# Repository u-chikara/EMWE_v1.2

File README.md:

# EMWE_v1.2

2024年度NHK高専ロボコンに出場したロボット「ひまり」と「ほしかご」に搭載していたメインマイコンボードの設計図です。

メインプロセッサ：ATSAME54N19A
統合開発環境：MPLAB

主な機能

CAN-FD 2チャンネル

SERCOM 5チャンネル（そのうち2チャンネルはコントローラと液晶用）

一応９軸IMUも付けられる

100M Ethernet

USB OTG （Type-CとTypeAをスイッチで切り替え）

SD/MMCカードスロット　マイコンに専用の回路があるのでそれで通信する

LEDとタクトスイッチをそれぞれ３つ搭載

今後のロボコンにお役立てください。

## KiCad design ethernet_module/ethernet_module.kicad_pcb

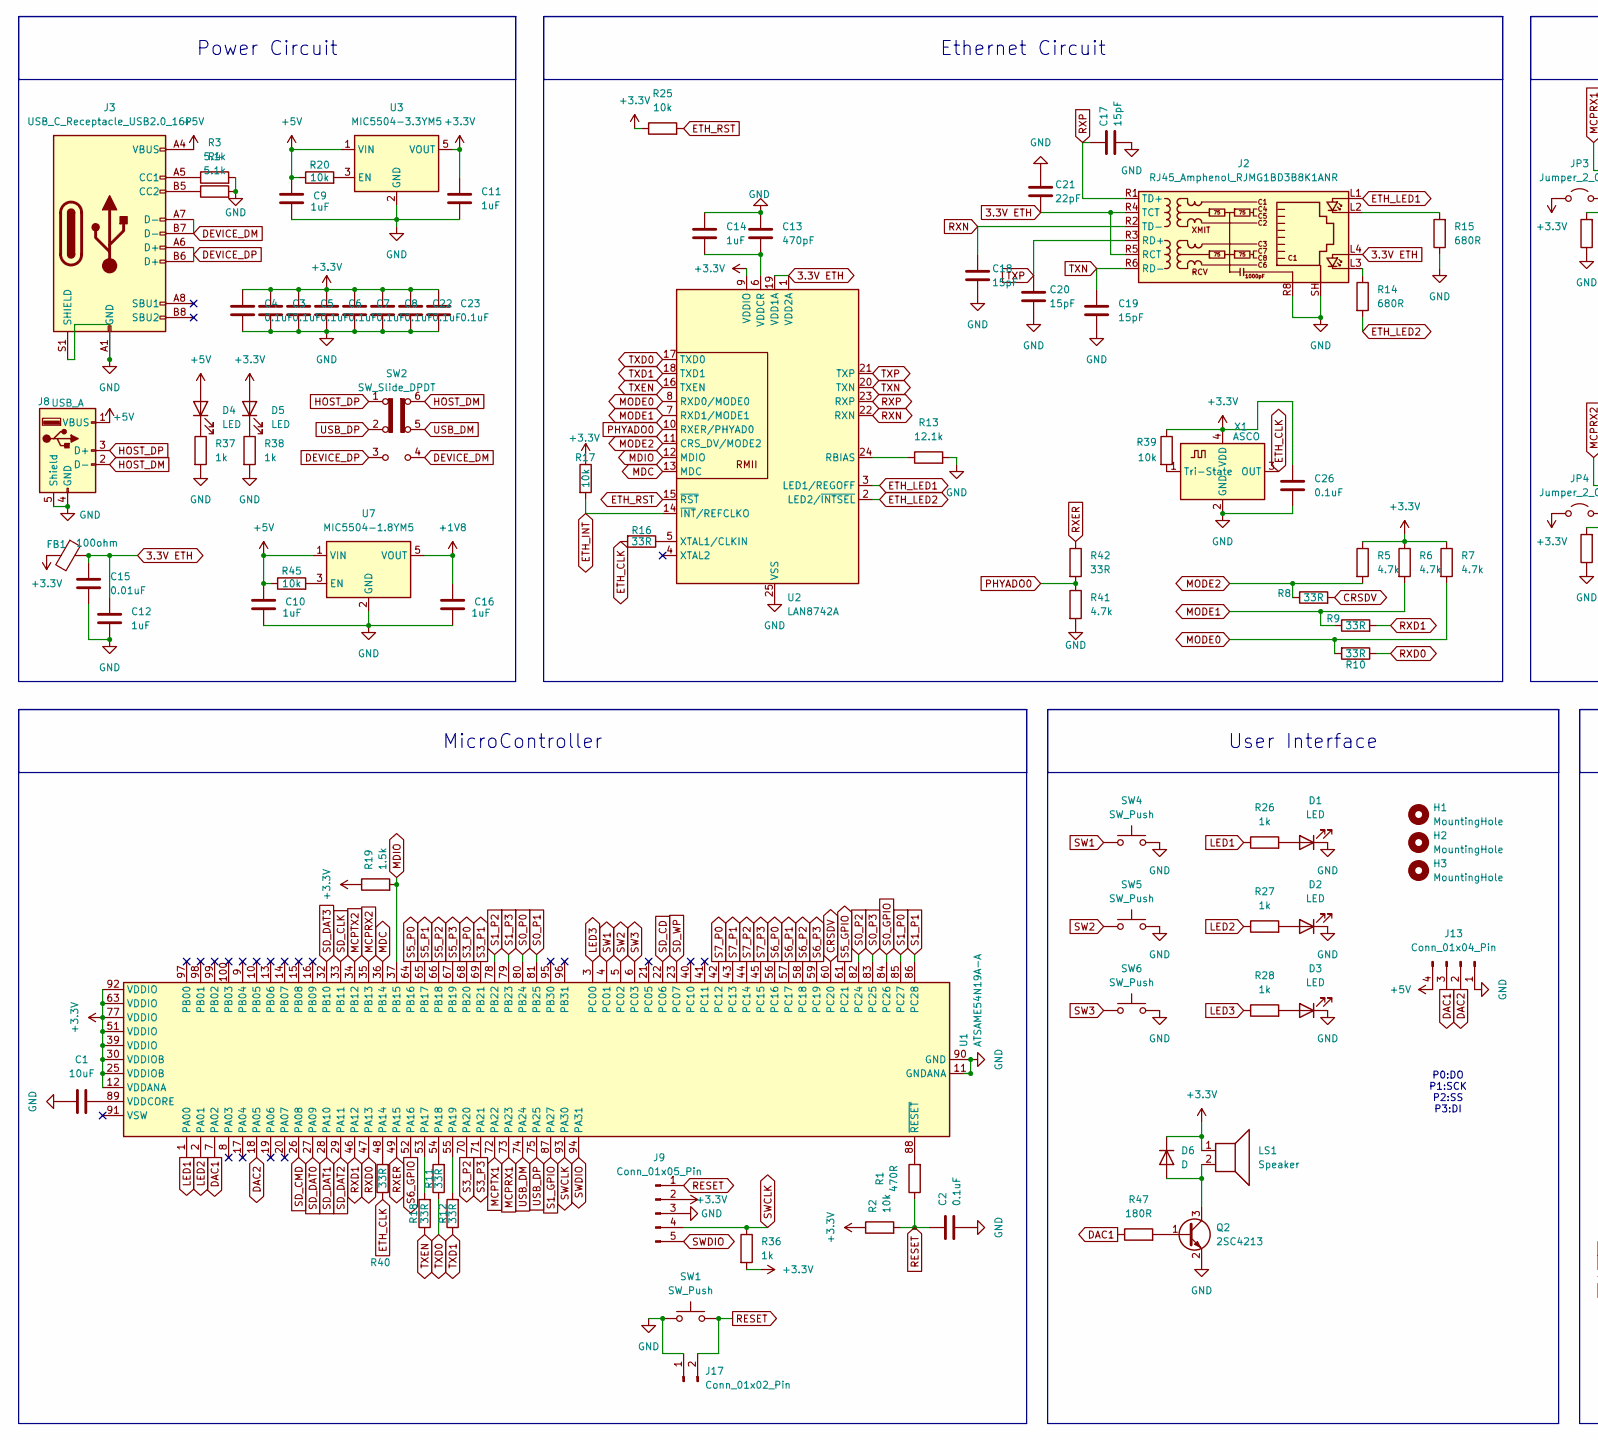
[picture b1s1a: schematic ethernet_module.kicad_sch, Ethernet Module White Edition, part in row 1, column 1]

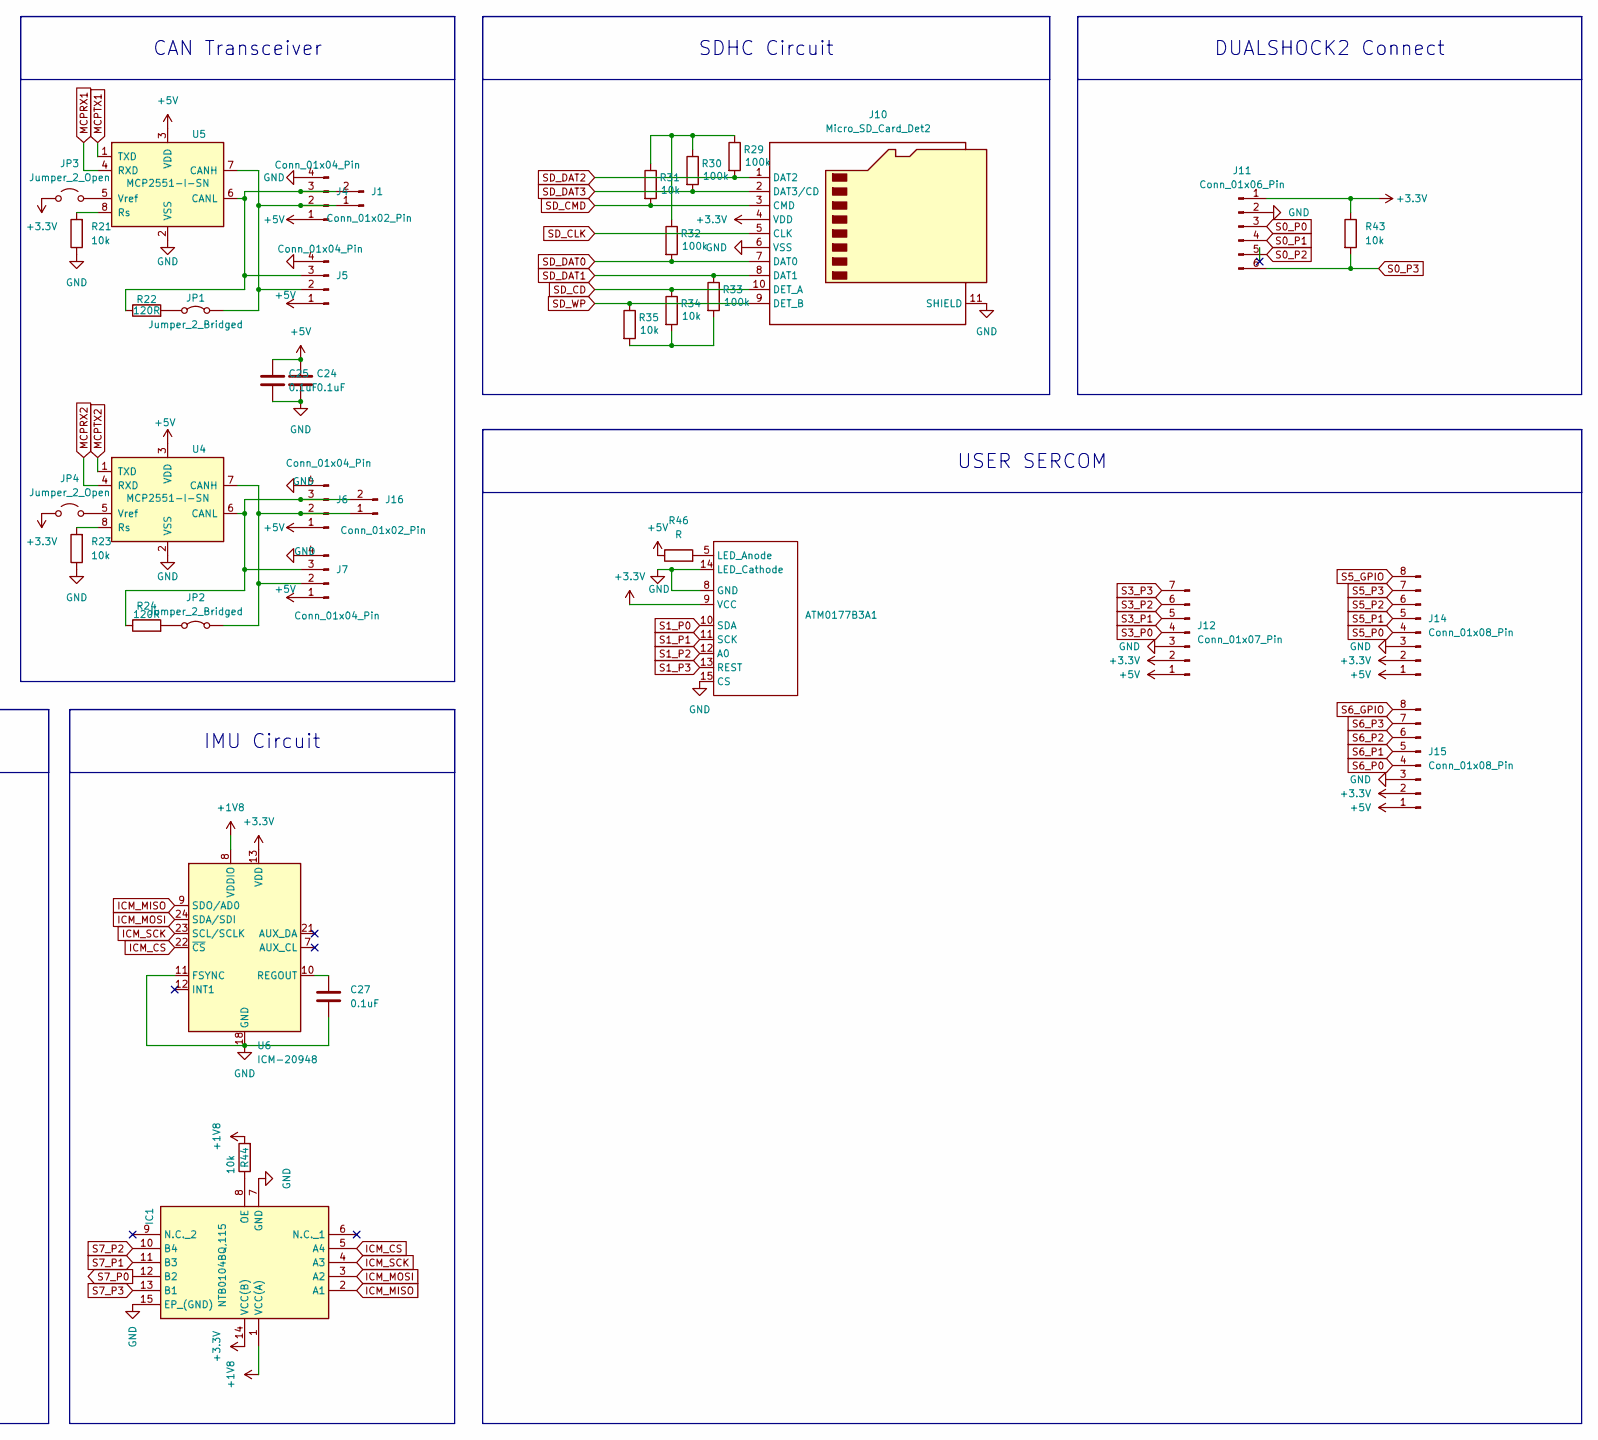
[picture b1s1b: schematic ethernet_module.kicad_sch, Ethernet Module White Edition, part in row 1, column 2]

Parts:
ATM0177B3A1: ATM0177B3A
C1: 10uF; R_0805_2012Metric
C2, C3, C4, C5, C6, C7, C8, C22, C23, C24, C25, C26, C27: 0.1uF; R_0603_1608Metric
C9, C10, C11, C12, C14, C16: 1uF; R_0603_1608Metric
C13: 470pF; R_0603_1608Metric
C15: 0.01uF; R_0603_1608Metric
C17, C18, C19, C20: 15pF; R_0603_1608Metric
C21: 22pF; R_0603_1608Metric
D1, D2, D3, D4, D5: LED; LED_0603_1608Metric
D6: D; D_0603_1608Metric
FB1: 100ohm; R_0603_1608Metric
H1, H2, H3: MountingHole; MountingHole_2.2mm_M2_Pad
IC1: NTB0104BQ,115; NTB0104BQ115; Manufacturer_Part_Number NTB0104BQ,115; Mouser Part Number 771-NTB0104BQ115
J1, J16, J17: Conn_01x02_Pin; PinHeader_1x02_P2.54mm_Vertical
J2: RJ45_Amphenol_RJMG1BD3B8K1ANR
J3: USB_C_Receptacle_USB2.0_16P; USB_C_Receptacle_GCT_USB4105-xx-A_16P_TopMnt_Horizontal
J4, J6: Conn_01x04_Pin; JST_XA_S04B-XASK-1_1x04_P2.50mm_Horizontal
J5, J7: Conn_01x04_Pin; JST_XA_B04B-XASK-1_1x04_P2.50mm_Vertical
J8: USB_A; USB_A_CONNFLY_DS1095-WNR0
J9: Conn_01x05_Pin; JST_PH_B5B-PH-K_1x05_P2.00mm_Vertical
J10: Micro_SD_Card_Det2; microSD_HC_Hirose_DM3AT-SF-PEJM5
J11: Conn_01x06_Pin; PinHeader_1x06_P1.27mm_Vertical
J12: Conn_01x07_Pin; PinHeader_1x07_P1.27mm_Vertical
J13: Conn_01x04_Pin; PinHeader_1x04_P1.27mm_Vertical
J14, J15: Conn_01x08_Pin; PinHeader_1x08_P1.27mm_Vertical
JP1, JP2: Jumper_2_Bridged; SolderJumper-2_P1.3mm_Open_RoundedPad1.0x1.5mm
JP3, JP4: Jumper_2_Open; SolderJumper-2_P1.3mm_Open_RoundedPad1.0x1.5mm
LS1: Speaker; PUIAudio_SMT_0825_S_4_R
Q2: 2SC4213; SOT-323_SC-70
R1: 470R; R_0603_1608Metric
R2, R17, R20, R21, R23, R25, R31, R34, R35, R39, R43, R44, R45: 10k; R_0603_1608Metric
R3, R4: 5.1k; R_0603_1608Metric
R5, R6, R7, R41: 4.7k; R_0603_1608Metric
R8, R9, R10, R11, R12, R16, R18, R40, R42: 33R; R_0603_1608Metric
R13: 12.1k; R_0603_1608Metric
R14, R15: 680R; R_0603_1608Metric
R19: 1.5k; R_0603_1608Metric
R22, R24: 120R; R_0603_1608Metric
R26, R27, R28, R36, R37, R38: 1k; R_0603_1608Metric
R29, R30, R32, R33: 100k; R_0603_1608Metric
R46: R; R_0603_1608Metric
R47: 180R; R_0603_1608Metric
SW1, SW4, SW5, SW6: SW_Push; SW_Push_1P1T_NO_CK_KMR2
SW2: SW_Slide_DPDT; SW_CK_JS202011CQN_DPDT_Straight
U1: ATSAME54N19A-A; TQFP-100_14x14mm_P0.5mm
U2: LAN8742A; VQFN-24-1EP_4x4mm_P0.5mm_EP2.5x2.5mm_ThermalVias
U3: MIC5504-3.3YM5; SOT-23-5
U4, U5: MCP2551-I-SN; SOIC-8_3.9x4.9mm_P1.27mm
U6: ICM-20948; InvenSense_QFN-24_3x3mm_P0.4mm
U7: MIC5504-1.8YM5; SOT-23-5
X1: ASCO; Oscillator_SMD_Abracon_ASE-4Pin_3.2x2.5mm

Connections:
3.3V ETH: C12.1, C15.1, C21.2, FB1.1, J2.L4, J2.R4 (TCT), J2.R5 (RCT), U2.1 (VDD2A), U2.19 (VDD1A)
+1V8: C16.1, IC1.1 (VCC(A)), R44.2, U6.8 (VDDIO), U7.5 (VOUT)
+3.3V: ATM0177B3A1.9 (VCC), C3.1, C4.1, C5.1, C6.1, C7.1, C8.1, C11.1, C22.1, C23.1, C26.1, D5.2 (A), D6.1 (K), FB1.2, IC1.14 (VCC(B)), J9.2, J10.4 (VDD), J11.1, J12.2, J14.2, J15.2, JP3.1 (A), JP4.1 (A), LS1.1, R2.1, R5.1, R6.1, R7.1, R17.1, R19.1, R25.1, R36.2, R39.1, R43.1, U1.12 (VDDANA), U1.25 (VDDIOB), U1.30 (VDDIOB), U1.39 (VDDIO), U1.51 (VDDIO), U1.63 (VDDIO), U1.77 (VDDIO), U1.92 (VDDIO), U2.9 (VDDIO), U3.5 (VOUT), U6.13 (VDD), X1.4 (VDD)
+5V: C9.1, C10.1, C24.1, C25.1, D4.2 (A), J3.A4 (VBUS), J3.A9 (VBUS), J3.B4 (VBUS), J3.B9 (VBUS), J4.1, J5.1, J6.1, J7.1, J8.1 (VBUS), J12.1, J13.4, J14.1, J15.1, R20.1, R45.1, R46.1, U3.1 (VIN), U4.3 (VDD), U5.3 (VDD), U7.1 (VIN)
CRSDV: R8.2, U1.60 (PC20)
DAC1: J13.3, R47.1, U1.7 (PA02)
DAC2: J13.2, U1.18 (PA05)
DEVICE_DM: J3.A7 (D-), J3.B7 (D-), SW2.4 (A)
DEVICE_DP: J3.A6 (D+), J3.B6 (D+), SW2.3 (C)
ETH_CLK: R16.2, R40.1, X1.3 (OUT)
ETH_INT: R17.2, U2.14 (~INT/REFCLKO)
ETH_LED1: J2.L1, U2.3 (LED1/REGOFF)
ETH_LED2: R14.2, U2.2 (LED2/~INTSEL)
ETH_RST: R25.2, U2.15 (~RST)
GND: ATM0177B3A1.8 (GND), ATM0177B3A1.14 (LED_Cathode), ATM0177B3A1.15 (CS), C1.1, C2.2, C3.2, C4.2, C5.2, C6.2, C7.2, C8.2, C9.2, C10.2, C11.2, C12.2, C13.1, C14.1, C15.2, C16.2, C17.2, C18.2, C19.2, C20.2, C21.1, C22.2, C23.2, C24.2, C25.2, C26.2, C27.2, D1.1 (K), D2.1 (K), D3.1 (K), IC1.7 (GND), IC1.15 (EP_(GND)), J2.R8, J2.SH, J3.A1 (GND), J3.A12 (GND), J3.B1 (GND), J3.B12 (GND), J3.S1 (SHIELD), J4.4, J5.4, J6.4, J7.4, J8.4 (GND), J8.5 (Shield), J9.3, J10.6 (VSS), J10.11 (SHIELD), J11.2, J12.3, J13.1, J14.3, J15.3, J17.1, Q2.2 (E), R3.2, R4.2, R13.2, R15.1, R21.1, R23.1, R37.2, R38.2, R41.2, SW1.1, SW4.2, SW5.2, SW6.2, U1.11 (GNDANA), U1.24 (GND), U1.31 (GND), U1.38 (GND), U1.50 (GND), U1.62 (GND), U1.76 (GND), U1.90 (GND), U2.25 (VSS), U3.2 (GND), U4.2 (VSS), U5.2 (VSS), U6.11 (FSYNC), U6.18 (GND), U6.20 (GND), U7.2 (GND), X1.2 (GND)
HOST_DM: J8.2 (D-), SW2.6 (C)
HOST_DP: J8.3 (D+), SW2.1 (A)
ICM_CS: IC1.5 (A4), U6.22 (~CS)
ICM_MISO: IC1.2 (A1), U6.9 (SDO/AD0)
ICM_MOSI: IC1.3 (A2), U6.24 (SDA/SDI)
ICM_SCK: IC1.4 (A3), U6.23 (SCL/SCLK)
LED1: R26.1, U1.1 (PA00)
LED2: R27.1, U1.2 (PA01)
LED3: R28.1, U1.3 (PC00)
MCPRX1: U1.73 (PA23), U5.4 (RXD)
MCPRX2: U1.35 (PB13), U4.4 (RXD)
MCPTX1: U1.72 (PA22), U5.1 (TXD)
MCPTX2: U1.34 (PB12), U4.1 (TXD)
MDC: U1.36 (PB14), U2.13 (MDC)
MDIO: R19.2, U1.37 (PB15), U2.12 (MDIO)
MODE0: R7.2, R10.2, U2.8 (RXD0/MODE0)
MODE1: R6.2, R9.1, U2.7 (RXD1/MODE1)
MODE2: R5.2, R8.1, U2.11 (CRS_DV/MODE2)
unnamed: ATM0177B3A1.5 (LED_Anode), R46.2
unnamed: D1.2 (A), R26.2
unnamed: D2.2 (A), R27.2
unnamed: D3.2 (A), R28.2
unnamed: D4.1 (K), R37.1
unnamed: D5.1 (K), R38.1
unnamed: D6.2 (A), LS1.2, Q2.3 (C)
unnamed: IC1.8 (OE), R44.1
unnamed: J1.1, J4.2, J5.2, JP1.2 (B), U5.7 (CANH)
unnamed: J1.2, J4.3, J5.3, R22.1, U5.6 (CANL)
unnamed: J2.L2, R15.2
unnamed: J2.L3, R14.1
unnamed: J3.A5 (CC1), R3.1
unnamed: J3.B5 (CC2), R4.1
unnamed: J6.2, J7.2, J16.1, JP2.2 (B), U4.7 (CANH)
unnamed: J6.3, J7.3, J16.2, R24.1, U4.6 (CANL)
unnamed: JP1.1 (A), R22.2
unnamed: JP2.1 (A), R24.2
unnamed: JP3.2 (B), U5.5 (Vref)
unnamed: JP4.2 (B), U4.5 (Vref)
unnamed: Q2.1 (B), R47.2
unnamed: R29.1, R30.1, R31.1, R32.1
unnamed: R33.2, R34.2, R35.2
unnamed: R40.2, U1.48 (PA14)
unnamed: R18.2, U1.53 (PA17)
unnamed: R11.2, U1.54 (PA18)
unnamed: R12.2, U1.55 (PA19)
unnamed: C1.2, U1.89 (VDDCORE)
unnamed: R1.2, U1.88 (~RESET)
unnamed: R13.1, U2.24 (RBIAS)
unnamed: C13.2, C14.2, U2.6 (VDDCR)
unnamed: R16.1, U2.5 (XTAL1/CLKIN)
unnamed: R20.2, U3.3 (EN)
unnamed: R23.2, U4.8 (Rs)
unnamed: R21.2, U5.8 (Rs)
unnamed: C27.1, U6.10 (REGOUT)
unnamed: R45.2, U7.3 (EN)
unnamed: R39.2, X1.1 (Tri-State)
PHYADO0: R41.1, R42.2, U2.10 (RXER/PHYAD0)
RESET: C2.1, J9.1, J17.2, R1.1, R2.2, SW1.2
RXD0: R10.1, U1.47 (PA13)
RXD1: R9.2, U1.46 (PA12)
RXER: R42.1, U1.49 (PA15)
RXN: C18.1, J2.R2 (TD-), U2.22 (RXN)
RXP: C17.1, J2.R1 (TD+), U2.23 (RXP)
S0_GPIO: U1.84 (PC26)
S0_P0: J11.3, U1.80 (PB24)
S0_P1: J11.4, U1.81 (PB25)
S0_P2: J11.5, U1.82 (PC24)
S0_P3: J11.6, R43.2, U1.83 (PC25)
S1_GPIO: U1.87 (PA27)
S1_P0: ATM0177B3A1.10 (SDA), U1.85 (PC27)
S1_P1: ATM0177B3A1.11 (SCK), U1.86 (PC28)
S1_P2: ATM0177B3A1.12 (A0), U1.78 (PB22)
S1_P3: ATM0177B3A1.13 (REST), U1.79 (PB23)
S3_P0: J12.4, U1.68 (PB20)
S3_P1: J12.5, U1.69 (PB21)
S3_P2: J12.6, U1.70 (PA20)
S3_P3: J12.7, U1.71 (PA21)
S5_GPIO: J14.8, U1.61 (PC21)
S5_P0: J14.4, U1.64 (PB16)
S5_P1: J14.5, U1.65 (PB17)
S5_P2: J14.6, U1.66 (PB18)
S5_P3: J14.7, U1.67 (PB19)
S6_GPIO: J15.8, U1.52 (PA16)
S6_P0: J15.4, U1.56 (PC16)
S6_P1: J15.5, U1.57 (PC17)
S6_P2: J15.6, U1.58 (PC18)
S6_P3: J15.7, U1.59 (PC19)
S7_P0: IC1.12 (B2), U1.42 (PC12)
S7_P1: IC1.11 (B3), U1.43 (PC13)
S7_P2: IC1.10 (B4), U1.44 (PC14)
S7_P3: IC1.13 (B1), U1.45 (PC15)
SD_CD: J10.10 (DET_A), R34.1, U1.22 (PC06)
SD_CLK: J10.5 (CLK), U1.33 (PB11)
SD_CMD: J10.3 (CMD), R31.2, U1.26 (PA08)
SD_DAT0: J10.7 (DAT0), R32.2, U1.27 (PA09)
SD_DAT1: J10.8 (DAT1), R33.1, U1.28 (PA10)
SD_DAT2: J10.1 (DAT2), R29.2, U1.29 (PA11)
SD_DAT3: J10.2 (DAT3/CD), R30.2, U1.32 (PB10)
SD_WP: J10.9 (DET_B), R35.1, U1.23 (PC07)
SW1: SW4.1, U1.4 (PC01)
SW2: SW5.1, U1.5 (PC02)
SW3: SW6.1, U1.6 (PC03)
SWCLK: J9.4, R36.1, U1.93 (PA30)
SWDIO: J9.5, U1.94 (PA31)
TXD0: R11.1, U2.17 (TXD0)
TXD1: R12.1, U2.18 (TXD1)
TXEN: R18.1, U2.16 (TXEN)
TXN: C19.1, J2.R6 (RD-), U2.20 (TXN)
TXP: C20.1, J2.R3 (RD+), U2.21 (TXP)
USB_DM: SW2.5 (B), U1.74 (PA24)
USB_DP: SW2.2 (B), U1.75 (PA25)

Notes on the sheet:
MicroController
User Interface
DUALSHOCK2 Connect
Ethernet Circuit
USER SERCOM
CAN Transceiver
IMU Circuit
Power Circuit
SDHC Circuit
P0:DO P1:SCK P2:SS P3:DI

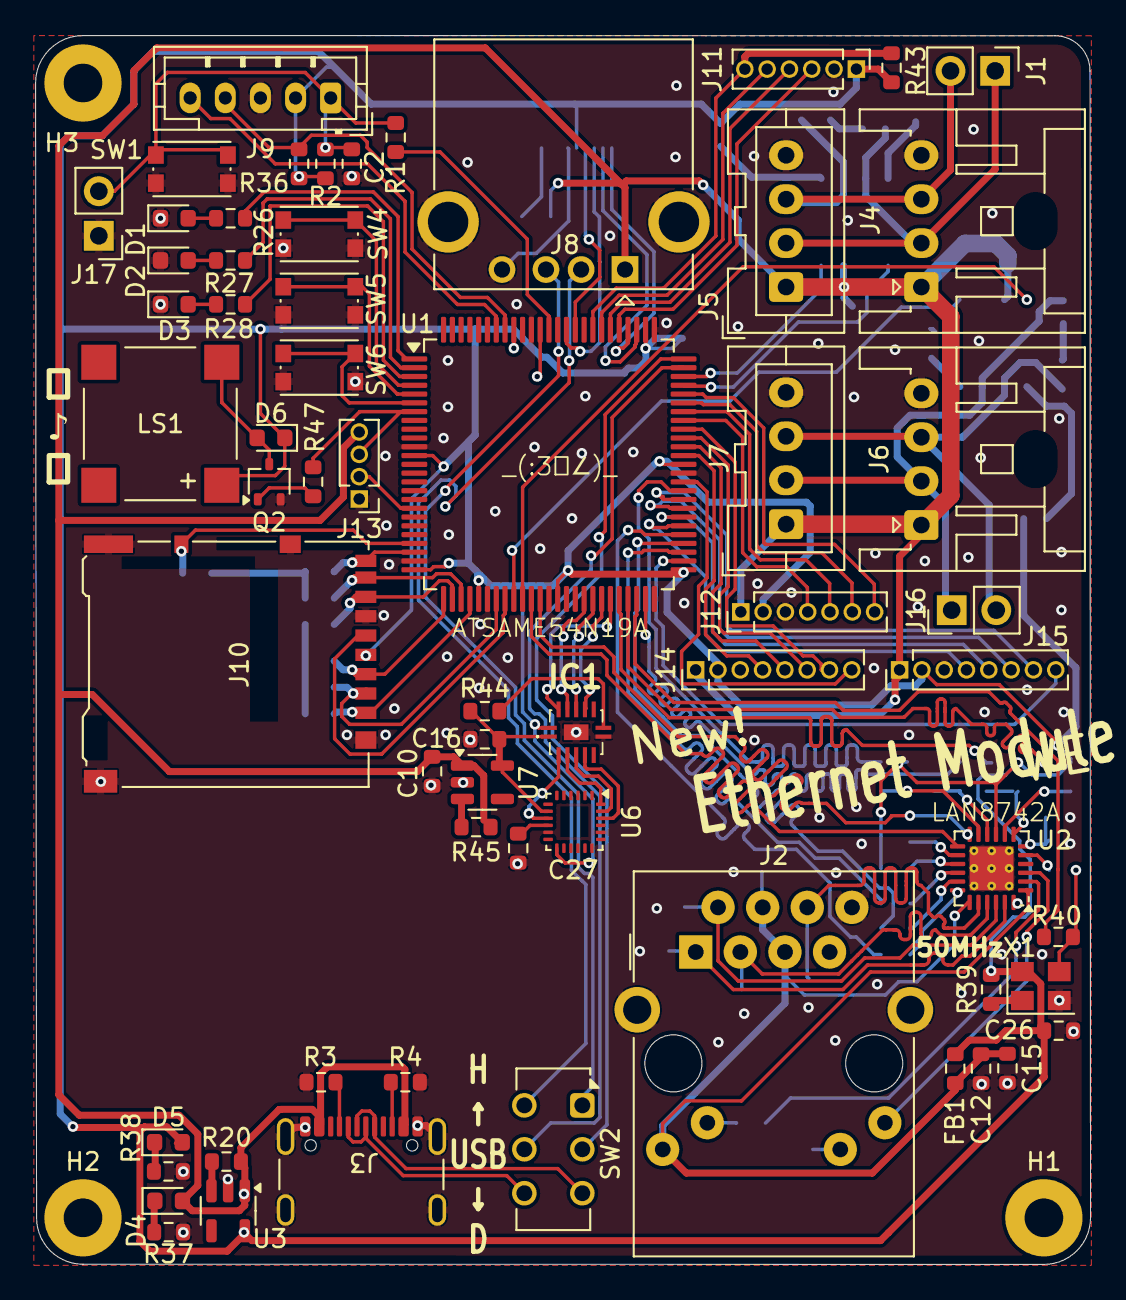
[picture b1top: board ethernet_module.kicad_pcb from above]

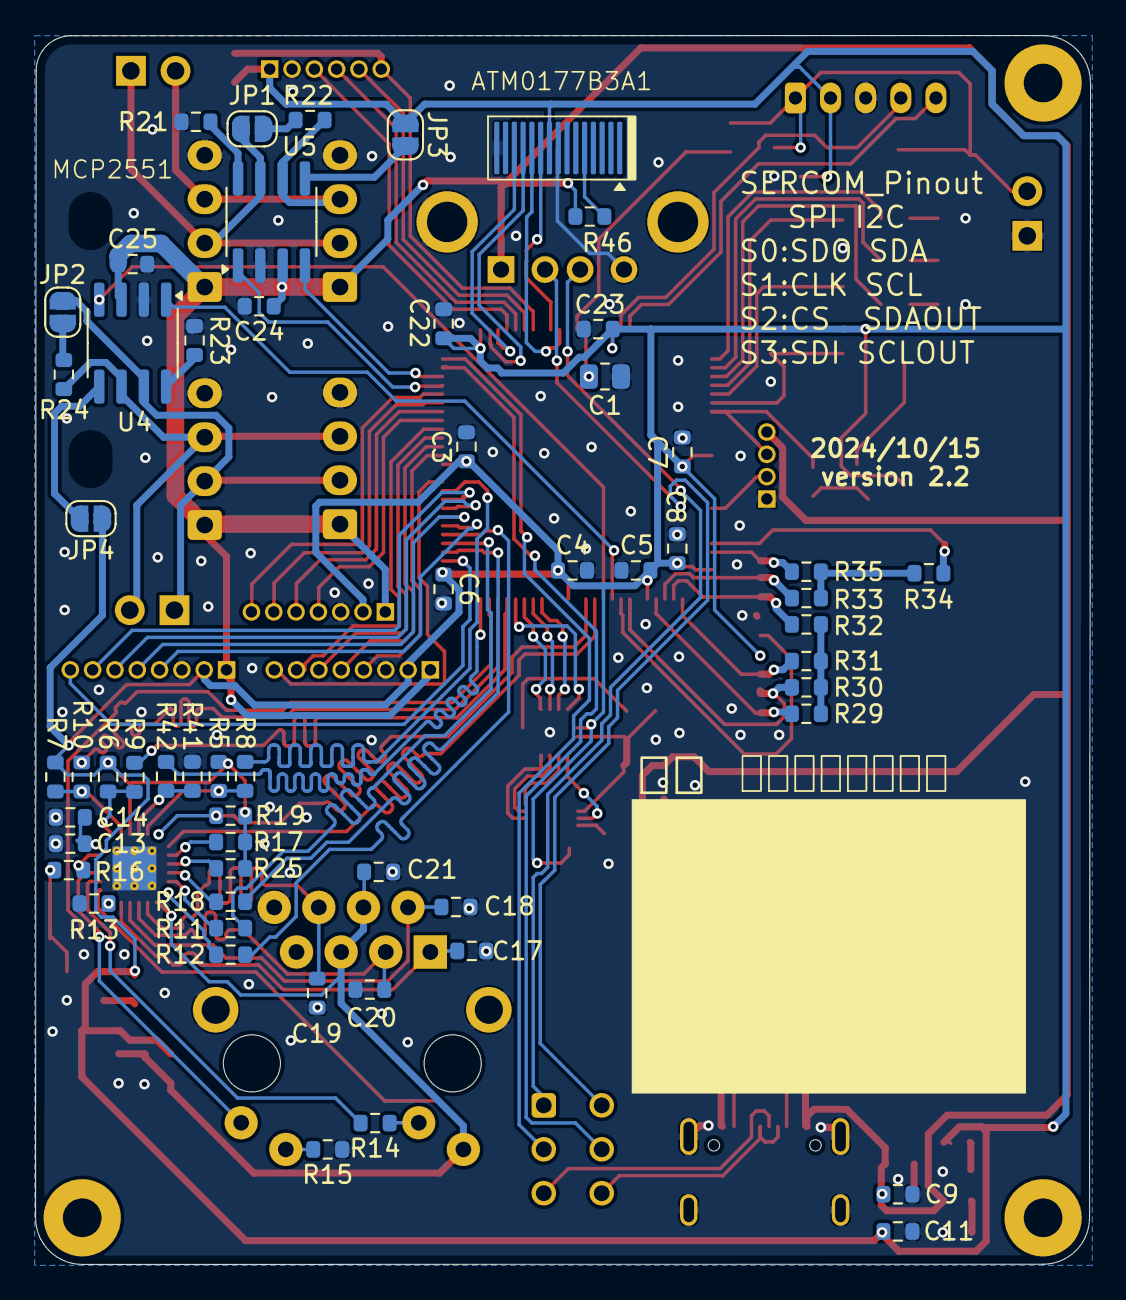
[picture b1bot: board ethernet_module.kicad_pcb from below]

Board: 2 copper layers, 60.1 x 70.0 mm, 122 parts (57 on the bottom side), 124 nets.
